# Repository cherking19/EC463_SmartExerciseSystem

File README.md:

# SeniorDesign_SmartExerciseSystem

Android:
Flutter compileSdkVersion, minSdkVersion, and targetSdkVersion changed to 33

https://stackoverflow.com/questions/72697570/warning-the-plugin-permission-handler-android-requires-android-sdk-version-33
https://pub.dev/packages/flutter_local_notifications#gradle-setup

- All app changes will happen on the smart_gym folder.

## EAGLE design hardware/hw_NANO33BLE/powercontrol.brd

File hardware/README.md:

# Smart Gym Hardware

Circuit Diagram of Arduino Nano 33 BLE, and connected power control circuit and haptic motor controller.

## Power Control Circuit

The power control circuit is designed to allow the user to power on the device with a single button press. The device will then remain powered on until the arduino sends an "off" signal (High/3.3V) from pin D12. This will cut off current from the connected Voltage Source (In this case, a 9V battery), and power off the arduino. 

The circuit is comprised of two NMOS transistors, a diode, and a resistor. The purpose of the first (top) transistor is to connect the positive terminal of the battery to the Vin pin. The transistor is opened by connecting the gate 9V, allowing the voltage source to pass to Vin. Once the arduino is powered on, the 5V output will turn on, and keep the first transistor open when the button is released. The diode prevents current from flowing back into the arduino when the button and 5V pins are both active. The second transistor will be off while the arduino is active, preventing any current flow from the 5V output, except for leakage. When the software determines that the arduino is inactive and will shut down, the second transistor is opened by setting D12 to HIGH. This pulls the gate of the first transistor to 0V, which turns off the transistor, and cuts off power to the arduino. Some current will pass through the resistor via the 5V pin very briefly.

This method powers on/off the device as soon as the button is pressed / the HIGh signal is sent to the second transistor.

## Haptic Motor
The Haptic Motor is controlled by a simple BJT transitor, modulated by pin D11, connected through a resistor and a diode to the BJT's gate. This allows current to flow from the 9V source through the motor when D11 is set to HIGH. In software, D11 can be set to HIGH for brief moments to activate the vibrate function. 

(Prototype)

Arduino code:
In addition to library manager libraries: https://github.com/FemmeVerbeek/Arduino_LSM9DS1
library manager libraries: Adafruit_AHRS, ArduinoBLE

NOTE: In order to use the 5V pin, you must solder the VUSB pad

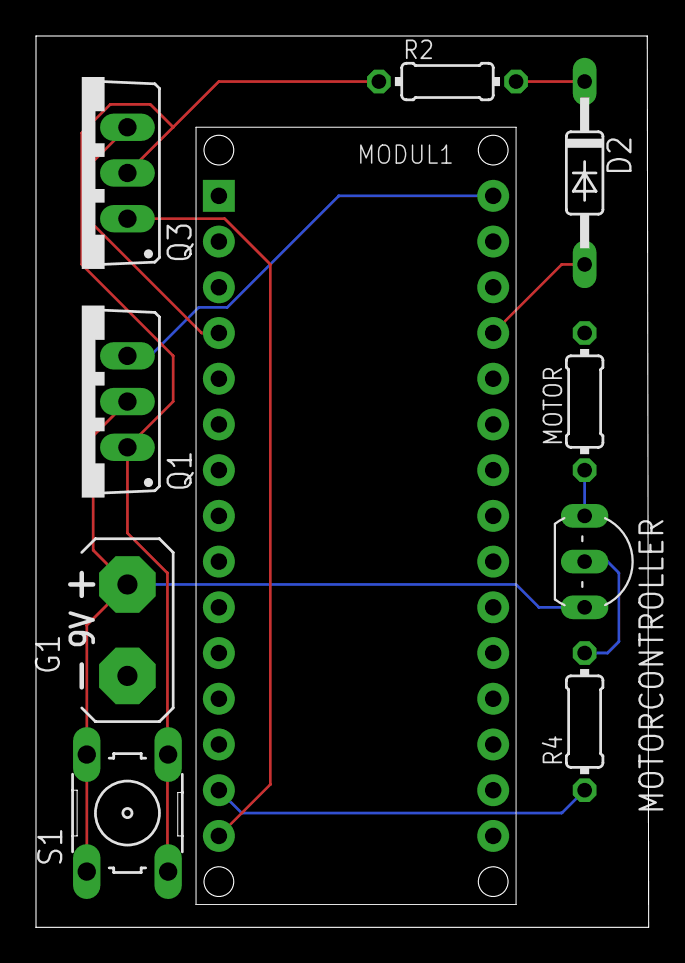
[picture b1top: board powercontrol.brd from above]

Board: 2 copper layers, 34.0 x 49.5 mm, 10 parts (0 on the bottom side), 11 nets.

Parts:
D2: 1N4148DO35-10; DO35-10
G1: AB9V
MODUL1: ARDUINO_NANO2
MOTOR: 1K; 0204/7
MOTORCONTROLLER: TO92-EBC
Q1, Q3: IRF520; TO220BV
R2, R4: 1K; 0204/7
S1: B3F-10XX

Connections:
5V: D2.A, MODUL1.J2.4
9V: G1.+, MOTORCONTROLLER.C, Q1.D, S1.1, S1.2
D11: MODUL1.J1.14, R4.1
D12: MODUL1.J1.15, Q3.G
DIODE_TO_RESISTOR: D2.C, R2.2
GND: G1.-, MODUL1.J2.2, MOTOR.2
GND2: MODUL1.J1.4, Q3.S
HAPTIC_GATE: MOTORCONTROLLER.B, R4.2
HAPTIC_VIN: MOTOR.1, MOTORCONTROLLER.E
POWERGATE: Q1.G, Q3.D, R2.1, S1.3, S1.4
VIN: MODUL1.J2.1, Q1.S

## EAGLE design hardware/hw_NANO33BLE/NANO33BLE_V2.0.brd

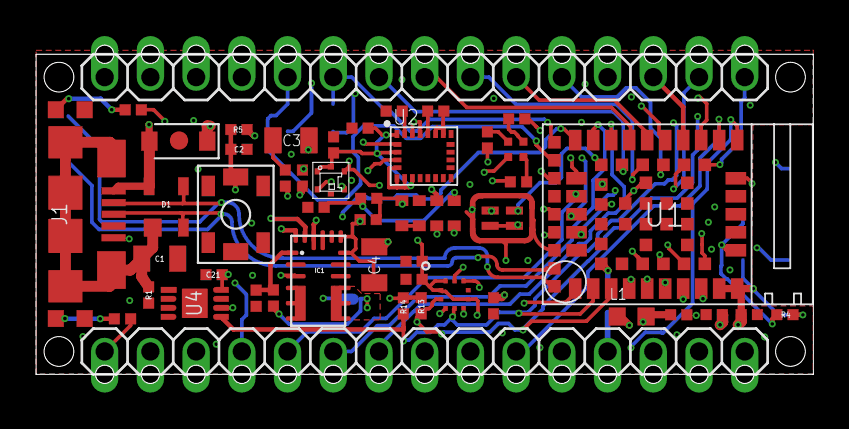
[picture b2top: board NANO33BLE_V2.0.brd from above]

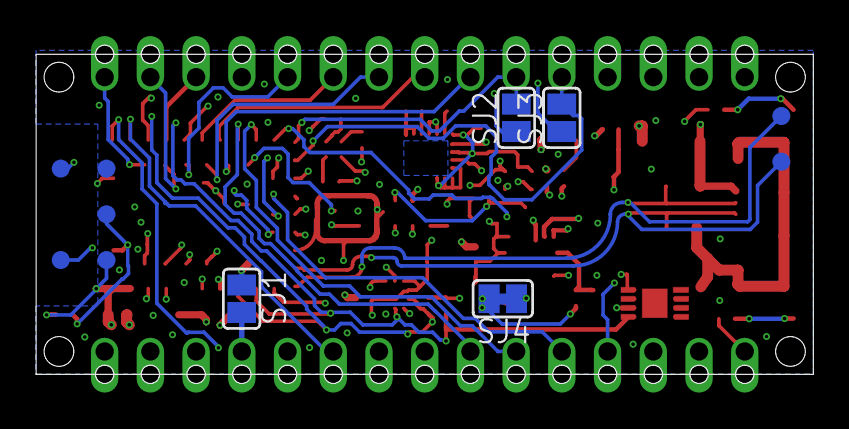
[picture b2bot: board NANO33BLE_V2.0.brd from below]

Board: 4 copper layers, 43.2 x 17.8 mm, 59 parts (4 on the bottom side), 61 nets.

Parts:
C1: 4n7; 0805-R2013X50N
C2, C5, C8, C9, C12, C21: 100n; 0402-1005X55N
C3, C4: 22u; 0805-R2013X50N
C6, C10: 1n; 0402-1005X55N
C7, C11, C13: 10n; 0402-1005X55N
C14: 4u7; 0402-1005X55N
C15, C16: 1u; 0402-1005X55N
D1: PRTR5V; SOT190P230X110-4N
D2: PMEG6020; SODFL3517X110N
D+: DNP; TP-1.00MM
D-: DNP; TP-1.00MM
DL1: YELLOW; LEDC1608X80N-AK
DL2: GREEN; LEDC1608X80N-AK
DL3: -; SMLP34RGB2W
FD1: DNP; FD-1-1.5
FRAME1: DNP; FRAME
HS-1: HTS221
IC1: MPM3610
J1: -; ZX62-AB-5PA
J3: DNP; 2X03-TP1
JP2, JP3: 1X15-CASTELL
L1: BLM18EG101; 0603-1608X90N
LPS-1: LPS22; LPS22H
PB1: PTS820; C&K_PTS820_NO_HOLES
R1: 1M; 0402-1005X55N
R2, R3: 330R; 0402-1005X55N
R4, R5: DNP; 0402-1005X55N
R6: 75k; 0402-1005X55N
R7, R11, R12: 1k; 0402-1005X55N
R8: 24k; 0402-1005X55N
R9: 39k; 0402-1005X55N
R10: 100k; 0402-1005X55N
R13, R14: 4k7; 0402-1005X55N
R15: 22R; 0402-1005X55N
SJ1, SJ2, SJ3, SJ4: DNP; SJ
U1: NINA-B3X
U2: LSM9DS1; LSM9DS1_TEMP_LGA24-8X4
U3: MP34DT06JTR; HCLGA
U4: DNP; SON50P300X200X60-9N-EP160X140
U5: APDS-9960; APDS9960

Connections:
+3V3: C3.1, C8.1, C9.2, C15.1, C21.1, DL3.1, J3.1, JP2.2, R4.2, R5.2, R15.2, SJ4.1, U1.9, U1.10, U4.8, U5.5
AIN0_A5/SCL: JP2.9, U1.18
AIN1_A7: JP2.11, U1.16
AIN2_A1: JP2.5, U1.27
AIN3_A0: JP2.4, U1.25
AIN4_A6: JP2.10, U1.17
AIN5_A3: JP2.7, U1.23
AIN6_A2: JP2.6, U1.24
AIN7_A4/SDA: JP2.8, U1.20
D2: JP3.5, U1.39
D3~: JP3.6, U1.21
D4: JP3.7, U1.40
D5~: JP3.8, U1.22
D6~: JP3.9, U1.41
D7: JP3.10, SJ2.2, U1.47
D8: JP3.11, SJ3.2, U1.48
D9~: JP3.12, U1.44
D10~: JP3.13, U1.36
GND: C1.2, C2.2, C3.2, C4.2, C5.1, C6.1, C7.1, C8.2, C9.1, C10.1, C11.1, C12.1, C13.1, C14.1, C15.2, C16.2, C21.2, DL1.C, DL2.C, HS-1.P$5.GND, IC1.3, IC1.12, IC1.13, IC1.14, J1.5, J3.5, JP2.14, JP3.4, LPS-1.3, LPS-1.5, LPS-1.8, LPS-1.9, PB1.1, PB1.2, PB1.3, PB1.4, PB1.5, R1.1, R8.1, R9.1, U1.6, U1.12, U1.14, U1.26, U1.30, U1.53, U1.GND@1, U1.GND@2, U1.GND@3, U1.GND@4, U1.GND@5, U1.GND@6, U1.GND@7, U1.GND@8, U1.GND@9, U1.GND@10, U1.GND@11, U1.GND@12, U2.19, U2.20, U3.GND, U3.GND@2, U3.GND@3, U3.GND@4, U4.4, U5.6
INT_APDS: U1.52, U5.2
LB: R12.1, U1.43
LG: R11.1, U1.4
LR: R7.1, U1.5
MIC_PWR: U1.51, U3.1, U3.2
MISO~: JP3.15, U1.34
MOSI: JP3.14, U1.35
unnamed: C1.1, D1.1, J1.6, J1.7, J1.8, J1.9, J1.10, J1.11, R1.2
unnamed: DL2.A, R2.1
unnamed: DL1.A, R3.1
unnamed: C5.2, U2.24
unnamed: IC1.1, R6.1, R8.2
unnamed: IC1.18, R9.2
unnamed: IC1.17, R10.1
unnamed: C7.2, U2.21
unnamed: U5.3, U5.4
unnamed: R2.2, U1.33
unnamed: DL3.3, R12.2
unnamed: DL3.2, R7.2
unnamed: DL3.4, R11.2
unnamed: JP2.12, SJ1.2
unnamed: C16.1, R15.1, U5.8
unnamed: IC1.7, IC1.8, IC1.9, IC1.20, R6.2, SJ4.2
NFC1: SJ2.1, U1.28
NFC2: SJ3.1, U1.29
PDMCLK: U1.42, U3.3
PDMDIN: U1.7, U3.4
RESETN: C2.1, J3.6, JP2.13, JP3.3, PB1.6, R5.1, U1.19
RX: JP3.2, U1.38
R_PULLUP: R13.2, R14.2, U1.8
SCK: JP2.1, R3.2, U1.1
SCL1: HS-1.P$2.SCL/SPC, LPS-1.2, R13.1, U1.3, U2.2, U4.6, U5.7
SDA1: HS-1.P$4.SDA/SDI/SDO, LPS-1.4, R14.1, U1.2, U2.4, U4.5, U5.1
SWCLK: J3.3, R4.1, U1.11
SWDIO: J3.2, U1.15
TX: JP3.1, U1.37
USB_N: D1.3, D-.X, J1.2, U1.55
USB_P: D1.2, D+.X, J1.3, U1.54
VBUS: C10.2, L1.2, SJ1.1, U1.31
VDD_ENV: C11.2, C12.2, C13.2, C14.2, HS-1.P$1.VDD, HS-1.P$6.CS, LPS-1.1, LPS-1.6, LPS-1.10, U1.49, U2.1, U2.3, U2.5, U2.6, U2.7, U2.8, U2.22, U2.23
VIN: C4.1, D2.C, IC1.16, JP2.15, R10.2
VUSB: C6.2, D1.4, D2.A, J1.1, L1.1

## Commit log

2022-10-27 Initial setup completed
2022-10-28 Add BottomNavigationBar with planned pages
2022-10-28 Start working on actually changing the view
2022-10-31 Change alignment of page title
2022-10-31 Add padding to the page title
2022-10-31 Reformat the pages so they're separate bodies
    4 add all pages for the app
2022-11-01 Add form validation
2022-11-02 Create workout classes and functionality for adding workouts
2022-11-10 Change exercise name and delete exercises
2022-11-14 Add set functionality
2022-11-16 Finish add delete sets (still need weight)
    can add new sets, can delete, can set reps same, can set rest time same. Need this for weight too
2022-11-16 Add weight field to form, start SharedPreferences
2022-11-17 Fix input bugs
2022-11-17 Added Login
2022-11-17 resolved conflict
2022-11-21 Initial setup of JSON code generation
2022-11-22 Finish set up JSON code generation and rudimentary SharedPreferences saving
2022-11-22 Organize file structure
2022-11-22 Fix organization
2022-11-22 Initial commit from bringing changes from previous branch
2022-11-28 Fix warnings
2022-11-29 Update dart.yml
    Changed working directory to correct one
2022-11-30 Added Ios
2022-11-30 Set up initial API
2022-12-01 Start reorganize workout widgets
2022-12-01 Start simplify form widgets
2022-12-01 Finish viewing workout
2022-12-03 Users can edit, save, and delete workouts now
2022-12-05 arduino example code to auto calibrate absolute orientation
2022-12-05 working serial curl demo 1 sensor
2022-12-05 Finish issue
2022-12-05 catch back case
2022-12-05 Fixed back button and added addworkout cloud function
2022-12-05 modified python script
2022-12-05 added printout
2022-12-05 test pixel overflow
2022-12-07 rebase to main branch
2022-12-09 Continue tracking interface
2022-12-12 Continue tracking
2022-12-13 Start timer
2022-12-13 Global Timer
2022-12-13 beautify progress bar
2022-12-14 polish app a little
2022-12-21 Finish tracking, introduce edit tracking workout
2022-12-29 Save and view in list view
    Users can now save a finished workout as history (in the SharedPreferences) and view it in the List view
2022-12-29 Merged BLE
2022-12-30 Finish view completed workout
2022-12-30 Complete issue
2022-12-31 Delete
2023-01-02 Initiate edit workout
2023-01-05 Added rootScaffoldMessengerKey to persist state
2023-01-05 finish
2023-01-08 SendOrientationValuesViaBLE
2023-01-10 Fix issue
2023-01-10 Fix workouts somehow got reversed
2023-01-11 Sort the lists based on which dates are before
2023-01-12 fix missing loadingspinner
2023-01-12 rebase
2023-01-12 resolve merge conflicts
2023-01-13 power controller arduino code and eagle cad schematic
2023-01-13 added code to control haptic motor, and circuit image
2023-01-16 updated circuit to add another diode
2023-01-16 updated ARHS filter to include magnetometer
2023-01-16 rename
2023-01-16 hardware README
2023-01-17 switched from lsm9ds1 library 1.0 to 2.0. added calibration code
2023-01-17 merged arduino files into one
2023-01-22 updated circuit
2023-01-23 Added Keep user sign in
2023-01-24 start fix
2023-01-24 Hello may need to revert
2023-01-24 fix some changes
2023-01-24 BLE_APP
2023-01-27 Save changes
2023-01-31 Logo Changed to Letter Circle Avatar
2023-01-31 Added comments
2023-02-01 fix merge conflicts and delete useless files
2023-02-03 README BLE
2023-02-03 BLE Display Values Continuously
2023-02-03 open tracking page when clicking on notif
2023-02-03 From Ben's PC
2023-02-04 BLE App separate folder deleted
2023-02-06 Android request notifications and fix open track route
2023-02-06 Finish conversion from list to map
2023-02-07 saving for changes
2023-02-09 Plan for exercise analysis
    This contains a breakdown of the approach that we decided to use to integrate our previously used python script with the smart gym app.
2023-02-09 Set up track workout page to be used to display sensors
2023-02-09 Move isSmartGymSensor function
    to a more global location in the blesettings.dart screen
2023-02-09 Remove superfluous comments
2023-02-09 Add custom exercises to exercise choices
2023-02-09 Update come back
2023-02-09 minSdkVersion
2023-02-10 save changes before rebase
2023-02-10 commit before flutter upgrade
2023-02-10 setup continuous sensor reading widgets (not tested)
2023-02-10 transfer
2023-02-10 multiple nodes
2023-02-12 single node skeleton
2023-02-12 2sensor
2023-02-12 Setup sensor provider
2023-02-14 starting to work on analyze_workout
2023-02-14 Development team
2023-02-17 save work
2023-02-17 Fix bug with multiple streams listened to and iOS device name
2023-02-18 curl
2023-02-18 comment
2023-02-18 calibration
2023-02-18 calibrated
2023-02-22 add gitignore
2023-02-22 haptic
2023-02-22 haptic_Arduino_code
2023-02-22 arduino_haptic
2023-02-22 First Test
2023-02-22 arduino_code
2023-02-23 haptic_arduino
2023-02-23 fixed absolute value check
2023-02-23 Create arduino_calibrations
2023-02-28 Automated integration
2023-02-28 Done merge
2023-03-02 hapticV2
2023-03-02 demo
2023-03-23 pcb in progress
2023-03-24 finished pcb
2023-03-24 added pcb gerber
2023-03-24 ignore
2023-03-28 arduino code
2023-03-28 Added to cycle light
2023-03-28 added curl feed back x2
2023-03-28 haptic_feedback_V2
2023-03-28 battery timeout
2023-04-13 Demo SPecs
2023-04-18 Added Press
2023-04-18 fixed arduino codes
2023-04-20 press
2023-05-03 add software flowchart images folder
2023-05-04 bug fixes
2023-05-05 Final Calibrated version

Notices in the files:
hardware/hw_NANO33BLE/NANO33BLE_V2.0.brd:
Copyright (c) 2016-2017 Arduino LLC.  All right reserved. EAGLE Design Rules
parts and their libraries:
Arduino-utility: This work is licensed under a Creative Commons Attribution-ShareAlike 4.0 International License.
Arduino-ucs: Copyright (c) 2016-2017 Arduino LLC.  All right reserved.
